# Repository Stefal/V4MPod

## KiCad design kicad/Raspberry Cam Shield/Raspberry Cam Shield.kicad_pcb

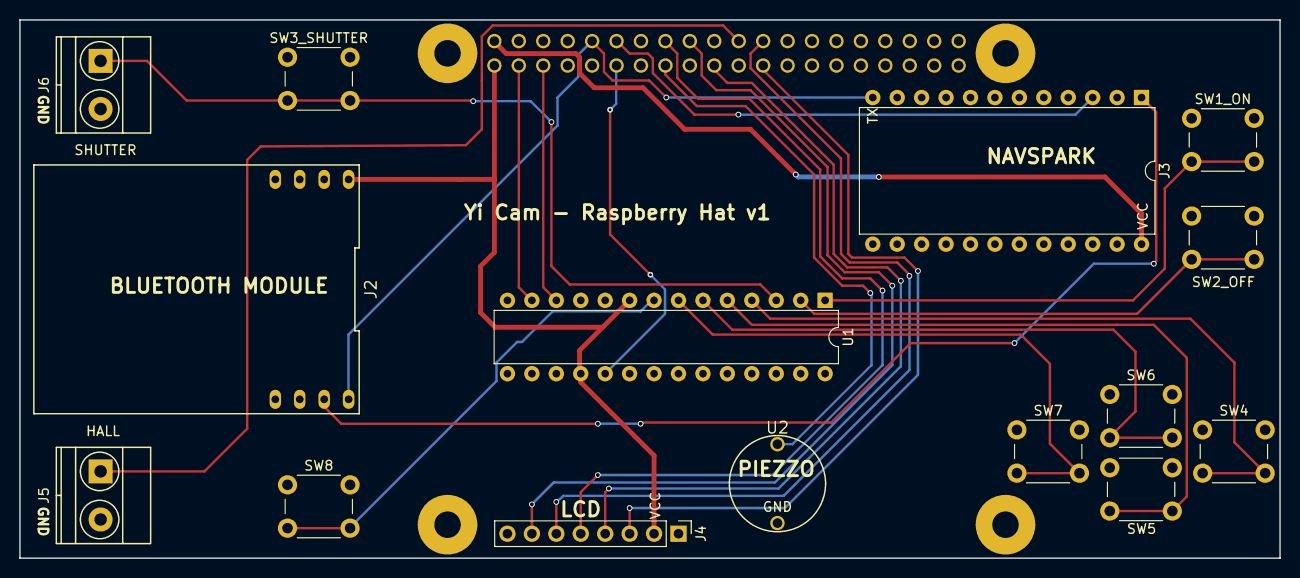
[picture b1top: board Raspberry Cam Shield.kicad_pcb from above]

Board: 2 copper layers, 131.0 x 55.9 mm, 16 parts (0 on the bottom side), 24 nets.

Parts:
J1: Raspberry_Pi_2_3; RASPBERRY_PI_HAT
J2: DIL8; DIP-8_2_ROW_W22.86_BLUETOOTH
J3: DIL24; DIP-24_W15.24mm
J4: CONN_01X08_LCD; Pin_Header_Straight_1x08_Pitch2.54mm
J5: Screw_Terminal_Hall_Sensor; TerminalBlock_Pheonix_MKDS1.5-2pol
J6: Screw_Terminal_Shutter_Switch; TerminalBlock_Pheonix_MKDS1.5-2pol
SW1_ON, SW2_OFF, SW3_SHUTTER, SW4, SW5, SW6, SW7, SW8: SW_PUSHBUTTON; SW_PUSH_6mm_h5mm
U1: MCP23017; DIP-28_W7.62mm
U2: BUZZER; PIEZZO_BUZZER

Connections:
+3V3: J1.1, J2.1, J4.2, U1.9, U1.18
/Battery_(5v): J1.2, J3.24
/CLK: J1.23, J4.3
/CS: J1.24, J4.6
/D/C: J1.16, J4.5
/DIN: J1.19, J4.4
/PPS: J1.12, J3.3
/RST: J1.18, J4.7
/TX: J1.10, J2.8, J3.12
GNDA: J1.39, J2.2, J3.21, J4.1, J5.2, J6.2, SW1_ON.1, SW2_OFF.1, SW3_SHUTTER.1, SW4.1, SW5.1, SW6.1, SW7.1, SW8.1, U1.10, U1.15, U1.16, U1.17, U2.2
unnamed: J1.3, U1.13
unnamed: J1.5, U1.12
unnamed: J1.11, U1.19
unnamed: J1.15, U2.1
unnamed: J1.22, J5.1
unnamed: J2.7, J3.1
unnamed: J6.1, SW3_SHUTTER.2, U1.3
unnamed: SW1_ON.2, U1.1
unnamed: SW2_OFF.2, U1.2
unnamed: SW4.2, U1.4
unnamed: SW5.2, U1.5
unnamed: SW6.2, U1.6
unnamed: SW7.2, U1.7
unnamed: SW8.2, U1.8

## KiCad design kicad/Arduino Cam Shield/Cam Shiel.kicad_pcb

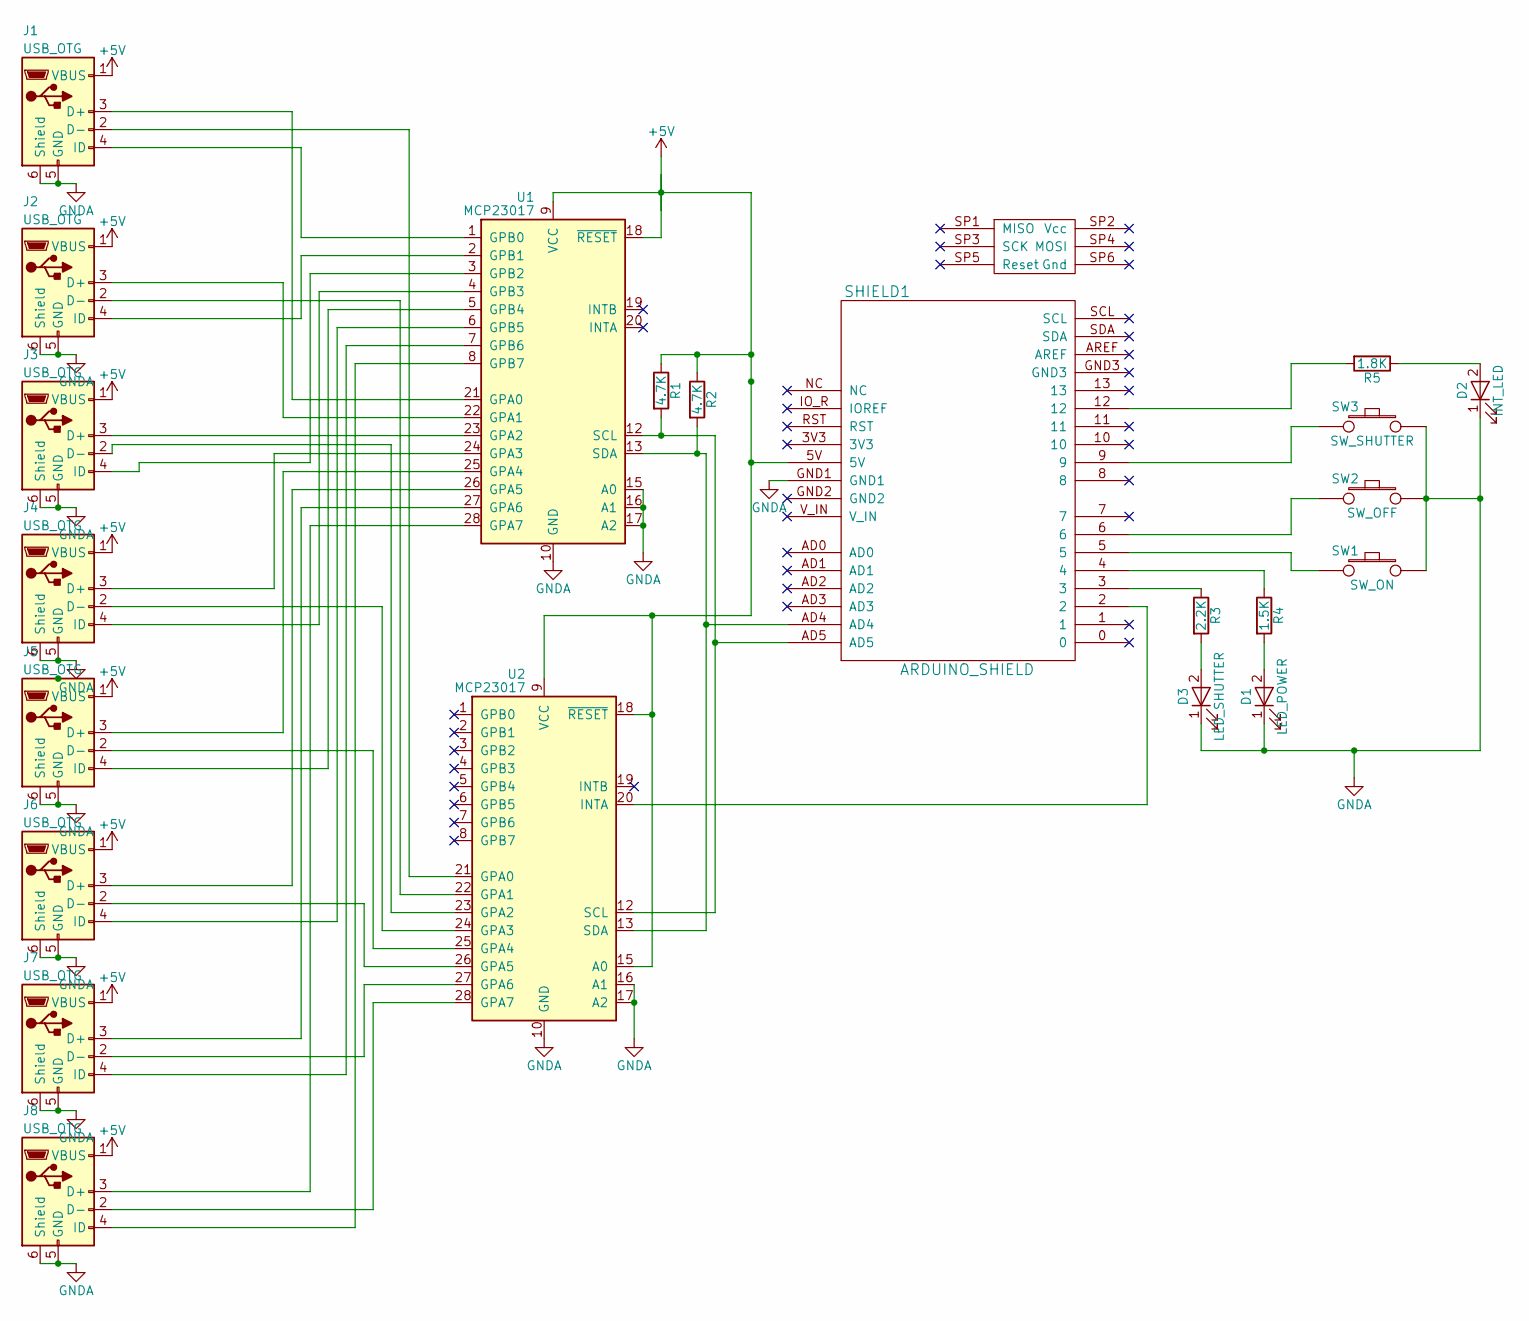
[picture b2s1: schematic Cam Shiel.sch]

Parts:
D1: LED_POWER; LED_0805
D2: INT_LED; LED_0805
D3: LED_SHUTTER; LED_0805
J1, J2, J3, J4, J5, J6, J7, J8: USB_OTG; USB_Micro-B_Molex-105017-0001
R1, R2: 4.7K; R_0805_HandSoldering
R3: 2.2K; R_0805_HandSoldering
R4: 1.5K; R_0805_HandSoldering
R5: 1.8K; R_0805_HandSoldering
SHIELD1: ARDUINO_SHIELD
SW1: SW_ON; SW_PUSH_6mm
SW2: SW_OFF; SW_PUSH_6mm
SW3: SW_SHUTTER; SW_PUSH_6mm
U1, U2: MCP23017; DIP-28_W7.62mm_Socket_LongPads

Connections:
+5V: J1.1 (VBUS), J2.1 (VBUS), J3.1 (VBUS), J4.1 (VBUS), J5.1 (VBUS), J6.1 (VBUS), J7.1 (VBUS), J8.1 (VBUS), R1.1, R2.1, SHIELD1.5V, U1.9 (VCC), U1.18 (~RESET), U2.9 (VCC), U2.15 (A0), U2.18 (~RESET); also elsewhere on the board
GNDA: D1.1 (K), D2.1 (K), D3.1 (K), J1.5 (GND), J1.6 (Shield), J2.5 (GND), J2.6 (Shield), J3.5 (GND), J3.6 (Shield), J4.5 (GND), J4.6 (Shield), J5.5 (GND), J5.6 (Shield), J6.5 (GND), J6.6 (Shield), J7.5 (GND), J7.6 (Shield), J8.5 (GND), J8.6 (Shield), SHIELD1.GND1, SW1.2, SW2.2, SW3.2, U1.10 (GND), U1.15 (A0), U1.16 (A1), U1.17 (A2), U2.10 (GND), U2.16 (A1), U2.17 (A2); also elsewhere on the board
unnamed: D1.2 (A), R4.2
unnamed: D2.2 (A), R5.1
unnamed: D3.2 (A), R3.2
unnamed: J1.2 (D-), U2.21 (GPA0)
unnamed: J1.3 (D+), U1.21 (GPA0)
unnamed: J1.4 (ID), U1.1 (GPB0)
unnamed: J2.2 (D-), U2.22 (GPA1)
unnamed: J2.3 (D+), U1.22 (GPA1)
unnamed: J2.4 (ID), U1.2 (GPB1)
unnamed: J3.2 (D-), U2.23 (GPA2)
unnamed: J3.3 (D+), U1.23 (GPA2)
unnamed: J3.4 (ID), U1.3 (GPB2)
unnamed: J4.2 (D-), U2.24 (GPA3)
unnamed: J4.3 (D+), U1.24 (GPA3)
unnamed: J4.4 (ID), U1.4 (GPB3)
unnamed: J5.2 (D-), U2.25 (GPA4)
unnamed: J5.3 (D+), U1.25 (GPA4)
unnamed: J5.4 (ID), U1.5 (GPB4)
unnamed: J6.2 (D-), U2.26 (GPA5)
unnamed: J6.3 (D+), U1.26 (GPA5)
unnamed: J6.4 (ID), U1.6 (GPB5)
unnamed: J7.2 (D-), U2.27 (GPA6)
unnamed: J7.3 (D+), U1.27 (GPA6)
unnamed: J7.4 (ID), U1.7 (GPB6)
unnamed: J8.2 (D-), U2.28 (GPA7)
unnamed: J8.3 (D+), U1.28 (GPA7)
unnamed: J8.4 (ID), U1.8 (GPB7)
unnamed 29: R1.2, SHIELD1.AD5, U1.12 (SCL), U2.12 (SCL); also elsewhere on the board
unnamed 30: R2.2, SHIELD1.AD4, U1.13 (SDA), U2.13 (SDA); also elsewhere on the board
unnamed 31: R3.1, SHIELD1.3; also elsewhere on the board
unnamed 32: R4.1, SHIELD1.4; also elsewhere on the board
unnamed 33: R5.2, SHIELD1.12; also elsewhere on the board
unnamed 36: SHIELD1.2, U2.20 (INTA); also elsewhere on the board
unnamed 37: SHIELD1.5, SW1.1; also elsewhere on the board
unnamed 38: SHIELD1.6, SW2.1; also elsewhere on the board
unnamed 41: SHIELD1.9, SW3.1; also elsewhere on the board

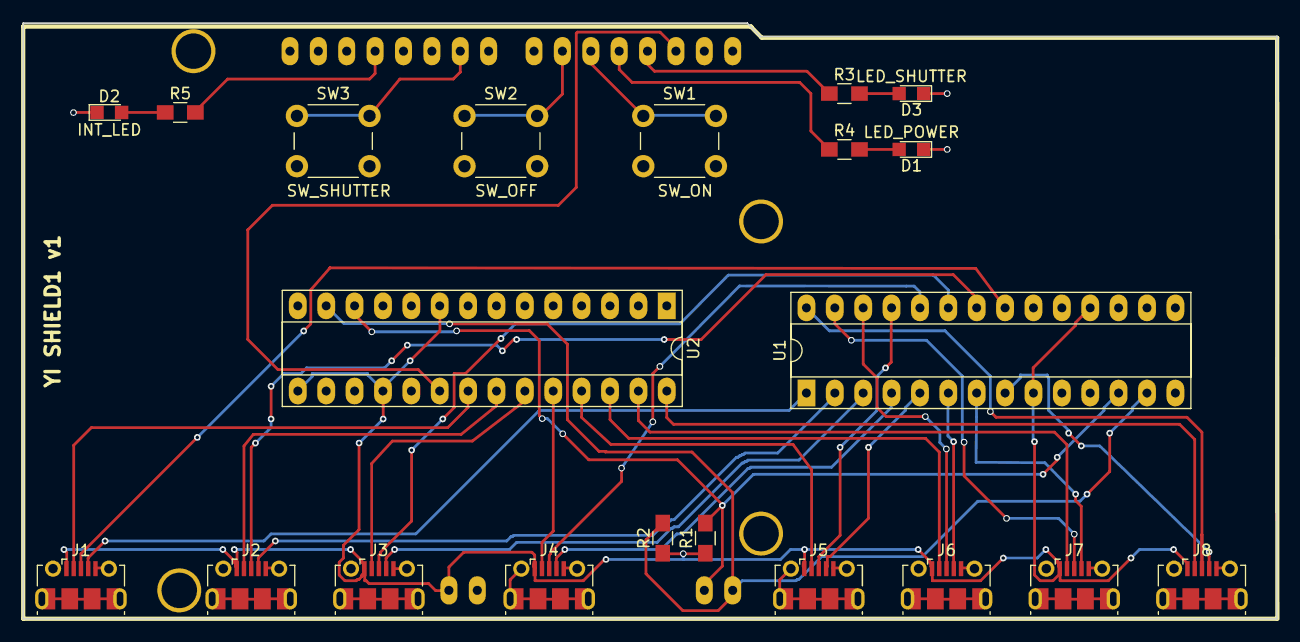
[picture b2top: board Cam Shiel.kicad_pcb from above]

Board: 2 copper layers, 112.2 x 53.3 mm, 22 parts (0 on the bottom side), 38 nets.

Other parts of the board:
YI SHIELD1 v1: ARDUINO_SHIELD

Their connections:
+5V: YI SHIELD1 v1.5V; also elsewhere on the board
GNDA: YI SHIELD1 v1.GND1; also elsewhere on the board
unnamed 29: YI SHIELD1 v1.AD4; also elsewhere on the board
unnamed 30: YI SHIELD1 v1.AD5; also elsewhere on the board
unnamed 31: YI SHIELD1 v1.3; also elsewhere on the board
unnamed 32: YI SHIELD1 v1.4; also elsewhere on the board
unnamed 33: YI SHIELD1 v1.12; also elsewhere on the board
unnamed 36: YI SHIELD1 v1.2; also elsewhere on the board
unnamed 37: YI SHIELD1 v1.5; also elsewhere on the board
unnamed 38: YI SHIELD1 v1.6; also elsewhere on the board
unnamed 41: YI SHIELD1 v1.9; also elsewhere on the board

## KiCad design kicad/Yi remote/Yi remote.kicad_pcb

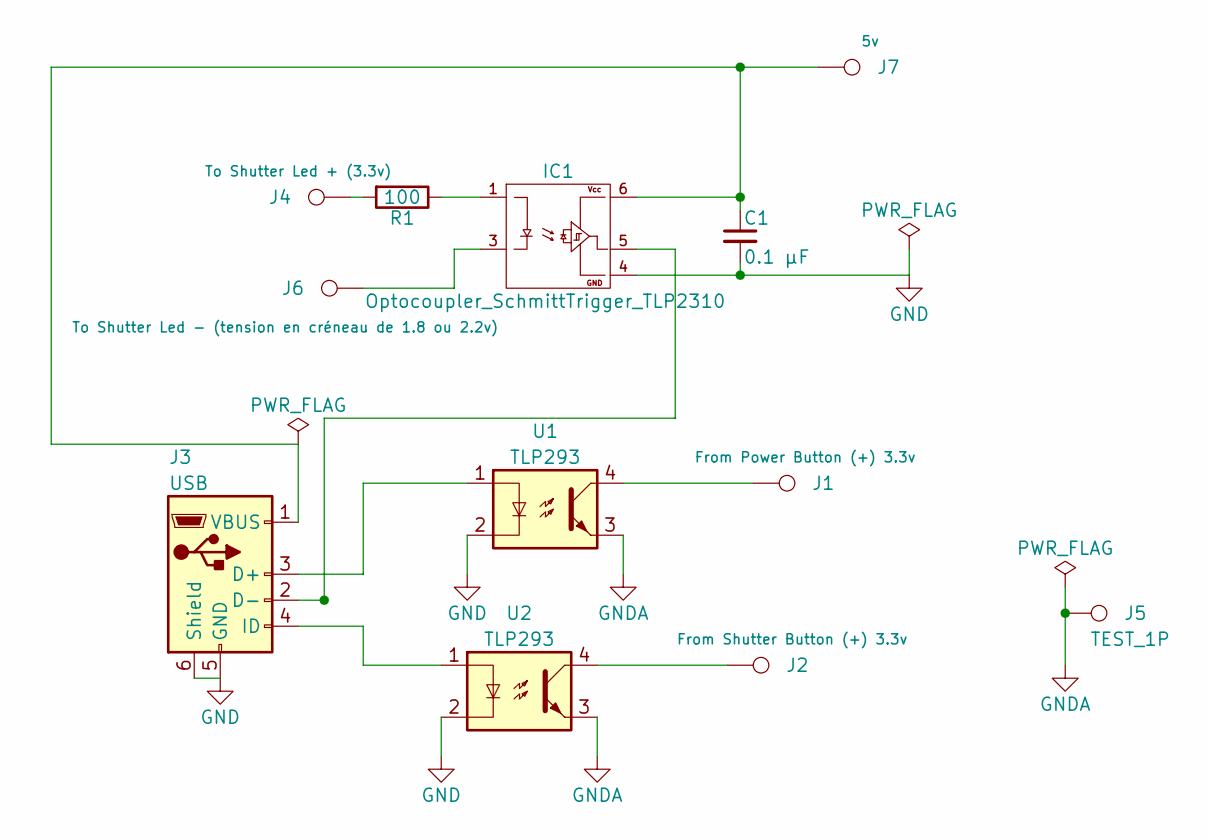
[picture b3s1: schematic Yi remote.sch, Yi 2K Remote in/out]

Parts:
C1: 0.1 µF; C_0402
IC1: Optocoupler_SchmittTrigger_TLP2310; SO-6_5_pins
J1: From Power Button (+) 3.3v; SolderWirePad_single_0-8mmDrill
J2: From Shutter Button (+) 3.3v; SolderWirePad_single_0-8mmDrill
J3: USB; USB_Mirco-B_Molex-105017-0001
J4: To Shutter Led + (3.3v); SolderWirePad_single_0-8mmDrill
J5: TEST_1P; SolderWirePad_single_0-8mmDrill
J6: To Shutter Led - (tension en créneau de 1.8 ou 2.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; SolderWirePad_single_0-8mmDrill
J7: 5v; SolderWirePad_single_0-8mmDrill
R1: 100; R_0402
U1, U2: TLP293; SOP-4_4.4x2.8mm_Pitch1.27mm_3D

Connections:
GND: C1.2, IC1.4, J3.5 (GND), J3.6 (Shield), U1.2, U2.2
GNDA: J5.1, U1.3, U2.3
unnamed: C1.1, IC1.6, J3.1 (VBUS), J7.1
unnamed: IC1.1, R1.1
unnamed: IC1.3, J6.1
unnamed: IC1.5, J3.2 (D-)
unnamed: J1.1, U1.4
unnamed: J2.1, U2.4
unnamed: J3.3 (D+), U1.1
unnamed: J3.4 (ID), U2.1
unnamed: J4.1, R1.2

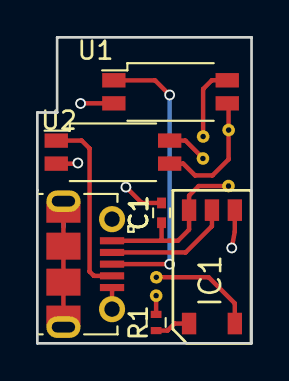
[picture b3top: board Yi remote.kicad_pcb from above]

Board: 2 copper layers, 11.9 x 17.0 mm, 12 parts (0 on the bottom side), 11 nets.

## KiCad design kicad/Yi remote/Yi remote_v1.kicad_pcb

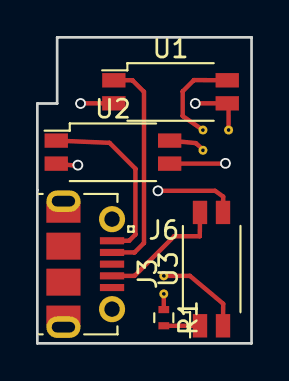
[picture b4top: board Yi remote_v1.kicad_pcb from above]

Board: 2 copper layers, 11.9 x 17.0 mm, 10 parts (0 on the bottom side), 10 nets.

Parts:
J1: To Power Button (+); SolderWirePad_single_0-8mmDrill
J2: To Shutter Button (+); SolderWirePad_single_0-8mmDrill
J3: USB; USB_Mirco-B_Molex-105017-0001
J4: To Shutter Led + (3.3v); SolderWirePad_single_0-8mmDrill
J5: TEST_1P; SolderWirePad_single_0-8mmDrill
J6: To Shutter Led - (1.8 ou 2.2v); SolderWirePad_single_0-8mmDrill
R1: 1,2K; R_0402
U1, U2: VO615A; SOP-4_4.4x2.8mm_Pitch1.27mm_3D
U3: SHT_LED; SOP-4_4.4x2.8mm_Pitch1.27mm_3D

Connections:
GND: J3.5, J3.6, U1.2, U2.2, U3.3
GNDA: J5.1, U1.3, U2.3
unnamed: J1.1, U1.4
unnamed: J2.1, U2.4
unnamed: J3.1, U2.1
unnamed: J3.2, U1.1
unnamed: J3.4, U3.4
unnamed: J4.1, R1.1
unnamed: J6.1, U3.2
unnamed: R1.2, U3.1

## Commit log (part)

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2017-02-03 Update copy_pic.py
    Documentation added
2017-02-03 Update copy_pic.py
    added type=int to cutoff args in argparse
2017-02-03 add positionnal argument
2017-02-09 add TODO comment
2017-02-10 Add source -> destination check
2017-02-10 Move the drivelist lenght checking
2017-02-10 Add intertime.py
2017-02-10 add move_picture.py
2017-02-12 Add --allgroups argument
2017-02-12 Indent
2017-02-15 add OsX support
2017-02-15 Remove unnecessary module
2017-02-15 More lower() for volumename check
2017-05-10 Adding arduino sketch
2017-05-12 update to use mcp interrupts
2017-05-14 interrupt management
2017-05-15 xor to or and various serial debug msg commented
2017-05-15 Add CmdMessenger
    Add CmdMessenger to control the Arduino with a Raspberry Pi +
    PyCmdMessenger
2017-05-31 Adding raspberry script
2017-09-04 Add PCB
    Internal Yi PCB
2017-09-05 Add PCB
2017-11-18 Adding correlate with log
    Adding the script that correlate the picture from the cams with the log
    generated on the raspberry pi
2017-11-18 add .gitignore
2017-11-18 reomve .pyc files
2017-11-18 More docstrings
2017-11-18 function rename
    function's name translation
2017-11-18 remove local setting
2017-11-19 More comments
2017-11-19 .gitignore
2017-11-20 Adding a loop on geotagging
2017-11-20 Revert "Adding a loop on geotagging"
    This reverts commit 328aa0586cf0cdb4bb6758f89205ab50bb8255da.
2017-11-20 Revert "Revert "Adding a loop on geotagging""
    This reverts commit a699972647335aa65504e1f7dd587400bdc0602b.
2017-11-20 Revert "Revert "Revert "Adding a loop on geotagging"""
    This reverts commit b85d497801b9b33cedd6fb828a390519795fa44b.
2017-11-20 indent correction
2017-11-20 bug correction
    missing str()
2017-11-20 various corrections
2017-11-20 Merge branch 'geotag-loop'
    # Conflicts:
    # correlate/correlate_with_log.py
2017-11-20 don't load the gpx in josm after a new geotag
2017-11-20 Exiting the script if no log or gpx/nmea were found.
2017-11-26 typo fix
2017-12-06 Add python script for the raspberry pi
2017-12-06 remove unused files
2017-12-06 New class for lcd menu
2018-03-06 add example
2018-05-13 luma
2018-05-13 New name for some functions
2018-05-13 Add speedometer Class
2018-05-13 better for loop
2018-05-13 some notes
2018-05-14 Convert odometer class to a threading object
2018-05-14 more doc
2018-05-15 Add shutter control class & example in odo.py
2018-05-15 class update from odo.py
2018-05-15 Retrieving the modified code from the use raspberry
2018-05-16 divers
2018-06-05 bug fix
    bug fix in parsing log
2018-06-29 Add correlate_with_log2
    Partial rewrite of correlate_with_log.
    Work in Progress
2018-07-02 Release for the new V4MBike with the handlebar remote
2018-07-24 first try to switch from Adafruit module to luma.lcd
2018-07-25 In progress
2018-07-25 Lcd Contrast
2018-08-17 new exif module
2018-08-17 fix big_delta folder location
2018-08-18 ignore
2018-08-18 add file path
2018-08-18 add sequence support
2018-08-19 fix: last sequence was missing
2018-08-20 move_picture doesn't use pyexiv2 anymore
2018-08-25 various
2018-08-28 Add hall sensor test script
2018-08-28 Add hall.py
2018-08-28 Fix int flag name
2018-09-18 Update hall
2018-09-21 Add V4mpack
2018-09-21 Import Queue instead of import from Needed for correct exception raising
2018-09-21 Update v4mpack
2018-09-24 Add Y2K telnet scripts
2018-09-27 Python 3 compatibility and some renaming
2018-09-27 Typo
2018-09-27 Creating a class to control the Yi2k
2018-09-27 Trying to use asyncio
2018-09-27 Add while loop to send new time
    The script will wait just before a new second to send the time to the
    cams
2018-09-30 Switch from pyexiv2 to Exifread
2018-09-30 Add other gnss talker id
    add beidou glonass and galileo talker id
2018-09-30 add talker id
    add generic talker id ($GN)
2018-09-30 gps_parser copy
2018-10-09 Add some conditions and more talker id
    Add some condition in correlate_with_log to check the metadata
    availability
    Add more gnss talkerId for a better nmea parser
2018-10-09 replace condition
2018-10-10 Cleanup
2018-10-10 add try/except to the send session function
2019-01-03 Adding a script to create the csv nedded for OpenPathView opv-make-lot
2019-01-04 Use image list with missing timestamp
    Use image list with missing timestamp inserted with
    insert_missing_timestamp function
2019-01-04 reduce standby duration
2019-01-04 bugfix: no path for virtual image
2019-01-04 Removing correlate.log from the .log search
2019-01-04 avg delta on 10%
2019-01-04 add condition on elevation interpolation
    When gpx are manually edited, elevation is sometime missing. In this
    case, after[3] could be "None".
    This commit add the condition to not have a float + None operand.
2019-01-04 Fix output encoding and line end
2019-01-20 Managing Case difference in path
2019-04-09 Add new session function
2019-04-09 convert copy_pic to python3
2019-04-15 convert code to python3
2019-04-15 fix AltitudeRef error in exif_write.py
    GPSAltitudeRef = 0 is for "Above Sea Level".
2019-04-16 remove waypoint parsing
2019-12-19 subsecondtimeoriginal fix
    Don't send subsecond to datetimeoriginal but to subsectimeoriginal
2020-01-29 intertime -> to python 3
2020-03-08 encoding corrections
2020-03-08 adding try/except on cam communication
2020-03-09 Adding try/except on sendind clock/settings to the Yi camera
2020-03-11 importing only Queue rather than full queue
2020-03-12 Adding class to control the Yi
2020-03-12 Adding parameter to start the script in interactive mode ( python3 v4mpack.py --interactive )
2020-03-13 Adding script needed to autostart V4Mpod at boot
2020-03-17 Update v4mpack.py
    First try with flask
2020-03-17 Updating web_gui Adding name argument to session file
2020-03-17 Updating web_gui
2020-03-18 Updating
2020-03-20 Adding a lot of things
2020-03-20 Adding Bootstrap
2020-03-22 Adding storage and battery request
2020-03-23 Updating Adding get and set settings Adding method to receive a picture path (useful for the first image in a new session)
2020-03-24 replace CRLF line ending to LF
2020-03-24 Adding web cam détails
2020-03-25 Updating single cam view
2020-03-26 Updating all cams view
2020-03-26 Adding timesync check check is PPS is really in use.
2020-03-27 Checking is a cam is already on/off before powering it off/on
2020-03-27 Adding function to change a cam parameters from the web gui
2020-03-27 adding new index web page
2020-03-28 Adding some css style to vertical align table's cells
2020-03-28 Moving css to its own file
2020-03-28 Serving bootstrap and jquery from static (no CDN)
2020-03-28 Adding very basic and insecure authentification access on the web gui
2020-03-28 Adding url to remember me where I found the flask-login tutorial
2020-03-29 Removing unuseful sys.exit
2020-03-30 Moving button class to the <a href=...>
2020-10-12 yi4k and gopro tools
2021-02-10 Fix empty space in subsec value
2021-02-10 Now only fix the time drift
2021-07-12 temp
2021-07-12 V4MPod upgrade to V6Mpod
2021-07-13 Adding U-Blox F9R config backup
2021-07-14 new preset for V6MPack
2021-07-15 Arduino update
    Update to compil the sketch with the official arduino app
2021-07-16 Update config.txt
    adding nmea gst message
2021-07-16 v4m -> v6m
2021-07-17 updating volume names
2021-07-26 fix typo
2021-07-30 add missing files and some fixes for python 3.8
2021-08-05 message on except
2021-08-05 convert session name to remove unwanted char In some cases it could break the gpspipe commande line
2022-04-14 Switch buzzer pin to 25 buzzer moved from the pcb to the manual shutter button enclosure
2022-04-14 disable fix mandatory at startup as it's not a good idea when I start the v6mpack indoor.
2022-04-14 refresh cams' clock every 60s. I was tired of waiting for the clock sync after 60 seconds without taking a picture.
2022-04-14 wrong route fixed. this route was called by http://localhost/favicon.ico
2022-04-15 Adding get all settings
2022-04-15 Using "future" for i/o with the cams. Cams webpage refresh is 6x faster
2022-04-15 Switch cams to photo mode
2022-04-15 Add favicon file
2022-04-15 More robust behaviour when a cam is suddenly off
2022-04-15 Adding a way to power up cam when status is unknown
2022-04-15 Adding future to get cams status
2022-04-15 Adding new buttons to web pages
2022-04-15 add profile
2022-04-15 Create config_F9R_V6MPack_firm1.21.txt
    Add configuration for new F9R firmware (1.21)
2022-07-29 Adding photo_filter
    Add photo_filter.py to find duplicate images and images in geofence zone
2022-07-29 fix first image not tested for geofence
2022-08-31 Update profile.cfg
    Adding profile for 360 images
2022-10-05 Add recursive arg
2022-10-06 fix answer decoding
2022-10-06 Add too tight angle detection
2022-10-06 new geofence exemple with null island
2022-10-06 more help messages
2022-11-23 removing included shapely module
2022-11-23 Update photo_filter.py
    bug fixes
2023-01-06 fix link to csv xsl file
2023-05-23 update for gopro hero11
2023-07-13 small fixes
2023-07-13 rtc_fix update for Hero 11
2023-08-21 ignore error for drive with accentuated name
2023-08-29 use future for parallel jpeg file searching
2023-08-29 function for groups creation
2023-08-29 cleaning
2023-08-29 Add user input to relaunch the group creation with a new cutoff value
2023-09-02 find mtp drive (linux)
2023-09-03 find marker file on SD
2023-09-03 fix empty result
2023-09-03 remove print
2023-09-03 display pic count for each group
2023-09-03 Adding delete pictures feature
2024-04-26 add add_gnss_accuracy
2024-05-11 adjust rtc fix
2024-05-30 WIP use nmea file
2025-09-11 add HERO13
